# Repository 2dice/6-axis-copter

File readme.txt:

■6軸コプター概要
6軸に移動可能なマルチコプターを6個のプロペラで実現することを目標としている．
最終的には自動で衝突回避・PCからコマンドを受信しアクロバットな動きをさせる．

■開発フェーズ
ラフ設計段階
・電子回路
	1x基板(コアレス->ブラシモータ)浮力不足により2xでブラシレスモータ試作
	2x基板作成中
・アクチュエータ
	ブラシレスモータ・プロペラ仮選定済み．2xで浮力確認
・ソフトウェア
	デバイスドライバ仮実装完了．
	2x基板作成後最終確認．その後モータ制御実装．
・筐体
	2x向け設計完了(3Dプリント中)

■ディレクトリ構成
./datasheet
	電子回路に使用している部品のデータシート置き場
./devlog
	開発記録
./schematic
	**.sch
		回路図(kicad)
	**.kicad_pcb
		基板図(kicad)
	librarys
		回路図に使用したライブラリ(kicad)
	gbr
		P板.com提出ファイル(板厚0.6mmで発注)
	**.pdf
		回路図
	**.FCStd
		筐体3D-CAD設計ファイル(FreeCAD)
	**.stl
		DMM.make提出ファイル(3Dプリンタ用STLファイル)
./src
	ソフトウェア
	環境構築は以下を参照
	http://qiita.com/2dice/items/70c5abf6259508660bce
./src/tools/6-axis-monitor
	無線通信(zigbee)によるモニタツール(Qt)
	zigbee環境構築方法は作成中

■構成
・プロペラ配置は3d図面及び./devlog/pictureを参照
・ブラシレスモータとリポバッテリ(3セル直列)を使用
・移動量は3軸ジャイロ及び3軸加速度センサでモニタ
・EEPROMにチューニングパラメータを保存
・測距センサを全軸に付け，衝突を回避するようなロジックを入れる
・デバイスの電源電圧の都合上4.5V/3.6Vの2電源を生成．
  本来I/Fにレベルシフタを入れるべきだが抵抗で保護し実力で故障回避を狙う．
  そのため電源電圧を極力近づける設計とした．

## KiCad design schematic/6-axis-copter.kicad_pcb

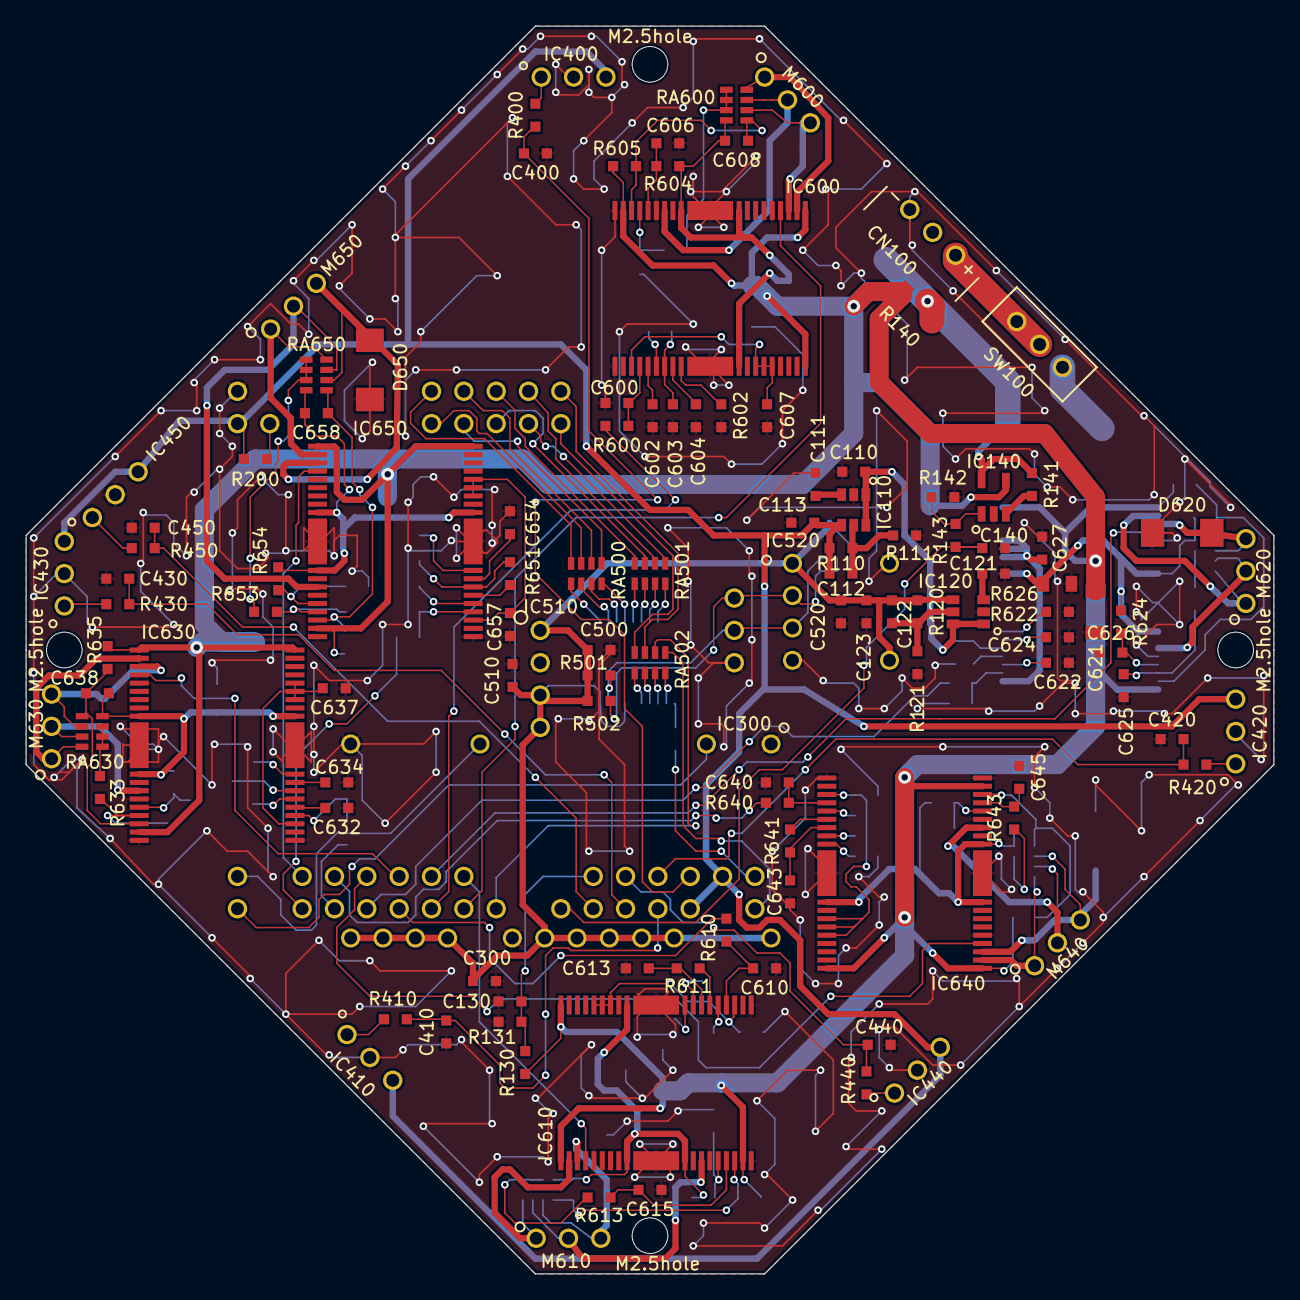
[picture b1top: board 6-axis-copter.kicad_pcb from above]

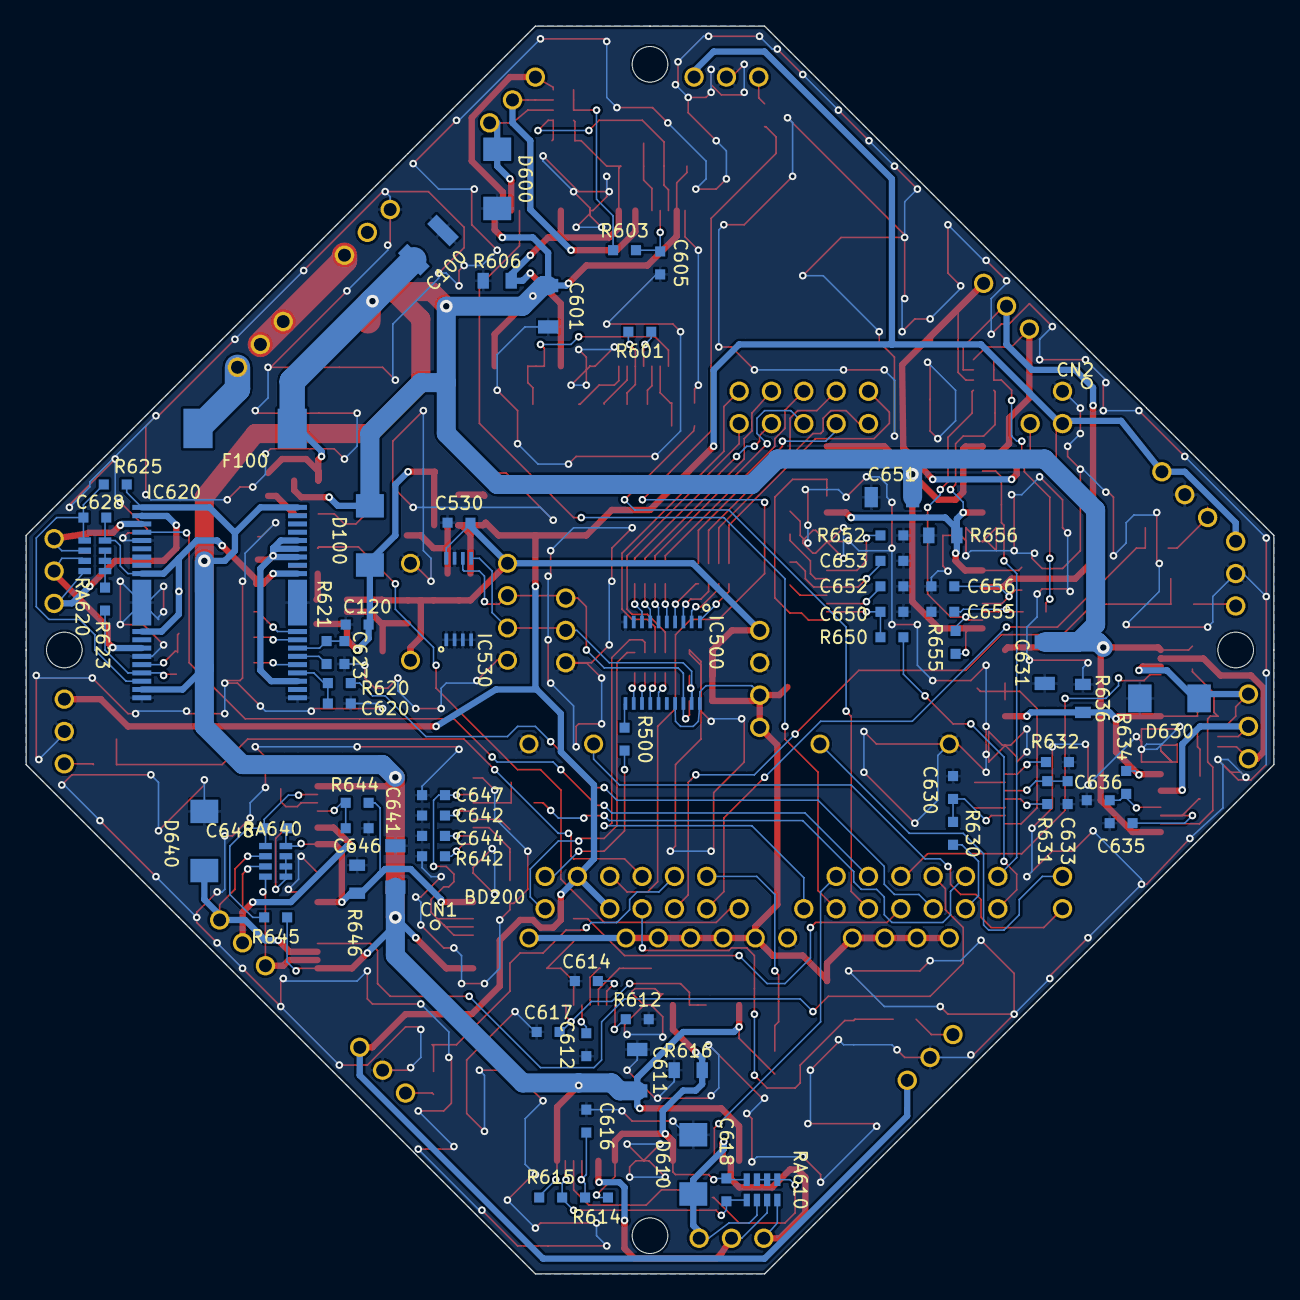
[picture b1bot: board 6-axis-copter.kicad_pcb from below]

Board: 2 copper layers, 98.0 x 98.0 mm, 188 parts (69 on the bottom side), 161 nets.

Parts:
BD200: H8-PRO
C100: 3225
C110, C111, C112, C113, C120, C121, C122, C123, C130, C140, C300, C400, C410, C420, C430, C440, C450, C500, C510, C520, C530, C600, C602, C603, C604, C605, C606, C607, C608, C610, C612, C613, C614, C615, C616, C617, C618, C620, C622, C623, C624, C625, C626, C627, C628, C630, C632, C633, C634, C635, C636, C637, C638, C640, C642, C643, C644, C645, C646, C647, C648, C650, C652, C653, C654, C655, C656, C657, C658: 1608
C601, C611, C621, C631, C641, C651: 3216
CN100: S3B-XH-A
D100, D600, D610, D620, D630, D640, D650: SR54F
F100: MF-SM300
IC110, IC120: SOT23-6
IC140: TSOP23-5
IC300: TWE-LITE
IC400, IC410, IC420, IC430, IC440, IC450: GP2Y0A21YK
IC500: TSSOP20
IC510: ADXL345
IC520: AE-L3GD20
IC530: TSSOP8
IC600, IC610, IC620, IC630, IC640, IC650: TB6588FG
M2.5hole, M2.5hole#2, M2.5hole#3, M2.5hole#4: M2.5hole
M600, M610, M620, M630, M640, M650: HK-AP05
R110, R111, R120, R121, R130, R131, R141, R142, R143, R200, R400, R410, R420, R430, R440, R450, R500, R501, R502, R600, R601, R602, R603, R604, R605, R610, R611, R612, R613, R614, R615, R620, R621, R622, R623, R624, R625, R630, R631, R632, R633, R634, R635, R640, R641, R642, R643, R644, R645, R650, R651, R652, R653, R654, R655: 1608
R140: 3216
R606, R616, R626, R636, R646, R656: 2012
RA500, RA501, RA502, RA600, RA610, RA620, RA630, RA640, RA650: BCN164AB
SW100: SS12D01G4

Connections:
+BATT: C601.1, C611.1, C621.1, C631.1, C641.1, C651.1, D100.1, IC140.4, IC600.1, IC600.17, IC600.36, IC610.1, IC610.17, IC610.36, IC620.1, IC620.17, IC620.36, IC630.1, IC630.17, IC630.36, IC640.1, IC640.17, IC640.36, IC650.1, IC650.17, IC650.36, R130.1, R140.2, R605.2, R615.2, R625.2, R635.2, R645.2, R655.2
/A0: BD200.61, RA502.7
/A1: BD200.62, RA502.8
/BAT_I: BD200.19, C140.1, R143.2
/BAT_V: BD200.18, C130.1, R130.2, R131.2
/D8: BD200.53, RA500.8
/D9: BD200.54, RA500.7
/D10: BD200.55, RA500.6
/D11: BD200.56, RA500.5
/D12: BD200.57, RA501.8
/D13: BD200.58, RA501.7
/D14: BD200.59, RA501.6
/D15: BD200.60, RA501.5
/DISTANCE_1: BD200.12, C400.1, R400.2
/DISTANCE_2: BD200.13, C410.1, R410.2
/DISTANCE_3: BD200.14, C420.1, R420.2
/DISTANCE_4: BD200.15, C430.1, R430.2
/DISTANCE_5: BD200.16, C440.1, R440.2
/DISTANCE_6: BD200.17, C450.1, R450.2
/MOTOR_1_IR: C608.1, IC600.9, IC600.10, IC600.28, R604.2, R606.1, RA600.4
/MOTOR_1_WAVEM: C608.2, IC600.16, R605.1, RA600.5
/MOTOR_2_IR: C618.1, IC610.9, IC610.10, IC610.28, R614.2, R616.1, RA610.4
/MOTOR_2_WAVEM: C618.2, IC610.16, R615.1, RA610.5
/MOTOR_3_IR: C628.1, IC620.9, IC620.10, IC620.28, R624.2, R626.1, RA620.4
/MOTOR_3_WAVEM: C628.2, IC620.16, R625.1, RA620.5
/MOTOR_4_IR: C638.1, IC630.9, IC630.10, IC630.28, R634.2, R636.1, RA630.4
/MOTOR_4_WAVEM: C638.2, IC630.16, R635.1, RA630.5
/MOTOR_5_IR: C648.1, IC640.9, IC640.10, IC640.28, R644.2, R646.1, RA640.4
/MOTOR_5_WAVEM: C648.2, IC640.16, R645.1, RA640.5
/MOTOR_6_IR: C658.1, IC650.9, IC650.10, IC650.28, R654.2, R656.1, RA650.4
/MOTOR_6_WAVEM: C658.2, IC650.16, R655.1, RA650.5
/MOTOR_DIR_1: BD200.25, IC600.4
/MOTOR_DIR_2: BD200.26, IC610.4
/MOTOR_DIR_3: BD200.28, IC620.4
/MOTOR_DIR_4: BD200.30, IC630.4
/MOTOR_DIR_5: BD200.32, IC640.4
/MOTOR_DIR_6: BD200.36, IC650.4
/MOTOR_PWM_1: BD200.27, R600.1
/MOTOR_PWM_2: BD200.29, R610.1
/MOTOR_PWM_3: BD200.31, R620.1
/MOTOR_PWM_4: BD200.33, R630.1
/MOTOR_PWM_5: BD200.34, R640.1
/MOTOR_PWM_6: BD200.35, R650.1
/ZIGBEE_Rx: BD200.39, IC300.3
/ZIGBEE_Tx: BD200.40, IC300.10
/~CS1: BD200.23, RA502.6
/~HWR: BD200.8, R500.2
/~RD: BD200.7, RA502.5
GND: BD200.41, C100.2, C110.2, C111.2, C113.2, C120.2, C121.2, C123.2, C130.2, C140.2, C300.2, C400.2, C410.2, C420.2, C430.2, C440.2, C450.2, C500.2, C510.2, C520.2, C530.2, C600.2, C601.2, C602.2, C603.2, C604.2, C605.2, C606.2, C607.2, C610.2, C611.2, C612.2, C613.2, C614.2, C615.2, C616.2, C617.2, C620.2, C621.2, C622.2, C623.2, C624.2, C625.2, C626.2, C627.2, C630.2, C631.2, C632.2, C633.2, C634.2, C635.2, C636.2, C637.2, C640.2, C641.2, C642.2, C643.2, C644.2, C645.2, C646.2, C647.2, C650.2, C651.2, C652.2, C653.2, C654.2, C655.2, C656.2, C657.2, CN100.1, D600.1, D610.1, D620.1, D630.1, D640.1, D650.1, IC110.2, IC120.2, IC140.2, IC300.1, IC300.14, IC300.20, IC400.2, IC410.2, IC420.2, IC430.2, IC440.2, IC450.2, IC500.10, IC510.2, IC510.7, IC520.4, IC520.8, IC530.1, IC530.2, IC530.3, IC530.4, IC530.7, IC600.5, IC600.13, IC600.18, IC600.19, IC600.37, IC600.38, IC610.5, IC610.13, IC610.18, IC610.19, IC610.37, IC610.38, IC620.5, IC620.13, IC620.18, IC620.19, IC620.37, IC620.38, IC630.5, IC630.13, IC630.18, IC630.19, IC630.37, IC630.38, IC640.5, IC640.13, IC640.18, IC640.19, IC640.37, IC640.38, IC650.5, IC650.13, IC650.18, IC650.19, IC650.37, IC650.38, R111.1, R121.1, R131.1, R142.1, R602.1, R606.2, R612.1, R616.2, R622.1, R626.2, R632.1, R636.2, R642.1, R646.2, R652.1, R656.2
unnamed: IC140.3, R141.1
unnamed: D630.2, IC630.3, M630.3, RA630.6
unnamed: C622.1, IC620.23
unnamed: C624.1, IC620.26
unnamed: C636.1, IC630.14, R634.1
unnamed: IC610.2, M610.1, RA610.8
unnamed: C617.1, IC610.21, IC610.30, IC610.31, IC610.32
unnamed: C604.1, IC600.26
unnamed: C612.1, IC610.23
unnamed: IC620.2, M620.1, RA620.8
unnamed: C627.1, IC620.21, IC620.30, IC620.31, IC620.32
unnamed: C614.1, IC610.26
unnamed: IC610.27, R612.2
unnamed: C637.1, IC630.21, IC630.30, IC630.31, IC630.32
unnamed: C635.1, IC630.15, R633.1
unnamed: IC630.27, R632.2
unnamed: IC630.24, R631.2
unnamed: C630.1, IC630.22, R630.2
unnamed: C633.1, IC630.25, R631.1
unnamed: C634.1, IC630.26
unnamed: C632.1, IC630.23
unnamed: C620.1, IC620.22, R620.2
unnamed: C623.1, IC620.25, R621.1
unnamed: IC620.24, R621.2
unnamed: C626.1, IC620.14, R624.1
unnamed: C625.1, IC620.15, R623.1
unnamed: IC620.27, R622.2
unnamed: D610.2, IC610.3, M610.3, RA610.6
unnamed: D620.2, IC620.3, M620.3, RA620.6
unnamed: R623.2, RA620.1, RA620.2, RA620.3
unnamed: C607.1, IC600.21, IC600.30, IC600.31, IC600.32
unnamed: C602.1, IC600.23
unnamed: IC600.2, M600.1, RA600.8
unnamed: IC620.12, M620.2, RA620.7
unnamed: IC650.27, R652.2
unnamed: C650.1, IC650.22, R650.2
unnamed: C653.1, IC650.25, R651.1
unnamed: IC650.24, R651.2
unnamed: C654.1, IC650.26
unnamed: C655.1, IC650.15, R653.1
unnamed: C652.1, IC650.23
unnamed: C644.1, IC640.26
unnamed: C647.1, IC640.21, IC640.30, IC640.31, IC640.32
unnamed: C642.1, IC640.23
unnamed: C656.1, IC650.14, R654.1
unnamed: IC650.2, M650.1, RA650.8
unnamed: R653.2, RA650.1, RA650.2, RA650.3
unnamed: C657.1, IC650.21, IC650.30, IC650.31, IC650.32
unnamed: D650.2, IC650.3, M650.3, RA650.6
unnamed: IC650.12, M650.2, RA650.7
unnamed: C646.1, IC640.14, R644.1
unnamed: IC640.27, R642.2
unnamed: C640.1, IC640.22, R640.2
unnamed: IC640.24, R641.2
unnamed: C643.1, IC640.25, R641.1
unnamed: R633.2, RA630.1, RA630.2, RA630.3
unnamed: IC630.12, M630.2, RA630.7
unnamed: IC630.2, M630.1, RA630.8
unnamed: D640.2, IC640.3, M640.3, RA640.6
unnamed: R643.2, RA640.1, RA640.2, RA640.3
unnamed: C645.1, IC640.15, R643.1
unnamed: IC640.12, M640.2, RA640.7
unnamed: IC640.2, M640.1, RA640.8
unnamed: IC500.12, RA502.4
unnamed: IC500.15, RA502.1
unnamed: BD200.44, R200.1
unnamed: C121.1, IC120.3
unnamed: CN100.3, SW100.1, SW100.2
unnamed: IC400.1, R400.1
unnamed: C122.2, IC120.5, R120.1, R121.2
unnamed: IC430.1, R430.1
unnamed: IC440.1, R440.1
unnamed: IC410.1, R410.1
unnamed: IC420.1, R420.1
unnamed: IC140.1, R142.2, R143.1
unnamed: F100.1, SW100.3
unnamed: C111.1, IC110.3
unnamed: C112.2, IC110.5, R110.1, R111.2
unnamed: IC500.14, RA502.2
unnamed: C100.1, F100.2, IC140.5, R140.1, R141.2
unnamed: C110.1, C120.1, D100.2, IC110.1, IC110.6, IC120.1, IC120.6
unnamed: IC500.18, IC510.9, IC520.2, IC530.6, R502.1
unnamed: IC500.19, IC510.8, IC520.3, IC530.5, R501.1
unnamed: IC500.6, RA501.2
unnamed: IC500.1, RA500.1
unnamed: IC500.2, RA500.2
unnamed: IC500.3, RA500.3
unnamed: IC500.4, RA500.4
unnamed: IC500.5, RA501.1
unnamed: IC500.7, RA501.3
unnamed: IC500.8, RA501.4
unnamed: IC500.11, R500.1
unnamed: IC500.13, RA502.3
unnamed: IC450.1, R450.1
unnamed: R603.2, RA600.1, RA600.2, RA600.3
unnamed: R613.2, RA610.1, RA610.2, RA610.3
unnamed: C606.1, IC600.14, R604.1
unnamed: D600.2, IC600.3, M600.3, RA600.6
unnamed: C605.1, IC600.15, R603.1
unnamed: IC600.12, M600.2, RA600.7
unnamed: C616.1, IC610.14, R614.1
unnamed: C613.1, IC610.25, R611.1
unnamed: IC610.12, M610.2, RA610.7
unnamed: C615.1, IC610.15, R613.1
unnamed: C610.1, IC610.22, R610.2
unnamed: IC610.24, R611.2
unnamed: C603.1, IC600.25, R601.1
unnamed: IC600.24, R601.2
unnamed: IC600.27, R602.2
unnamed: C600.1, IC600.22, R600.2
VCC: BD200.10, BD200.11, BD200.42, C112.1, C113.1, IC110.4, IC400.3, IC410.3, IC420.3, IC430.3, IC440.3, IC450.3, R110.2, R200.2
VDD: C122.1, C123.1, C300.1, C500.1, C510.1, C520.1, C530.1, IC120.4, IC300.15, IC300.16, IC300.17, IC300.18, IC300.21, IC300.22, IC300.23, IC300.24, IC300.25, IC300.28, IC500.17, IC500.20, IC510.1, IC510.3, IC510.4, IC520.1, IC520.5, IC530.8, R120.2, R501.2, R502.2

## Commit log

2014-08-23 書き込みテスト serialでhello worldを返すプログラム．水晶発振子25MHzでの書き込みテスト
2014-08-24 前プロジェクトを元にリファクタリング,VA=PA転送実装
2014-08-24 DRAM実装
2014-08-24 timer/timer割り込み実装
2014-08-24 周辺情報更新
2014-08-30 TIOCA0にPWM出力を実装
2014-08-30 TIOCA1にPWM出力を実装
2014-08-30 TIOCA2にPWM出力を実装
2014-08-30 TMO0にPWM出力を実装
2014-08-30 TMIO1にPWM出力を実装
2014-08-30 TMO2にPWM出力を実装
2014-08-31 makeでTAGSファイルを生成するようMakefileを修正
2014-08-31 IRQ5にプルアップ抵抗追加(オープンドレイン)
2014-09-06 回路図の不要な配線を削除
2014-09-07 AN0のAD値取得を実装
2014-09-08 AN1のAD値取得を実装
2014-09-08 リファクタリング(ADチャネルセレクトを汎用関数に切り出し)
2014-09-08 AN2~7のAD値取得を実装
2014-09-08 timer_init()からモータドライバの初期化を切り出してenable出力を追加
2014-09-15 I2Cバスコントローラ/加速度センサのデバイス情報追加
2014-09-15 TAGSファイルを生成する際に削除してから生成するように変更
2014-09-17 SCI2にzigbeeシリアル送信実装
2014-09-18 zigbeeからのコマンド受信割り込み実装
2014-09-20 SCI0をSCI1という記述に修正 SCI1に対し勘違いしてSCI0という名前をつけていたため
2014-10-04 I2Cバスコン及び加速度センサからのデータ読み出しを実装
2014-10-05 角速度センサからのデータ読み出しを実装
2014-10-05 リファクタリング(I2Cからの連続2バイト読みだし関数の変数名を汎用化)
2014-10-05 周辺情報の進捗更新
2014-10-05 角速度センサの読み出しを2バイト読み出しに変更
2014-10-05 モニタツール first commit(コンソールにD1の値のみを表示)
2014-10-05 モニタツールにD1を出力する簡易グラフ実装
2014-10-06 モニタツールで16進加速度データを物理値にして出力できるよう変更
2014-10-06 リファクタリング(データ格納関数を分離)
2014-10-06 モニタツールに全ての受信データ取り込みを実装
2014-10-08 モニタツールのAXにゼロ点補正と速度・距離計算を仮実装
2014-10-09 モニタツールの速度計算をブールの公式で再実装
2014-10-09 モニタツールに角度算出を実装(ブールの公式)
2014-10-11 回路図の配線ミスを修正
2014-10-11 回路図のバッテリーシンボル・フットプリント修正
2014-10-11 回路図のH8ボードフットプリントを修正
2014-10-11 回路図のモーターに直列にコイル追加
2014-10-11 回路図：DIP部品のサイズ修正
2014-10-11 回路図にバッテリーSW追加
2014-10-14 PCBボード図作成
2014-10-15 基板製造メーカー(P板.com)の指摘を元にPCBボード図を修正
2014-10-18 部品表作成
2014-10-18 readmeの進捗，ディレクトリ構成を更新
2014-10-26 周辺情報更新(筐体設計変更)
2014-10-31 周辺情報更新(筐体設計再変更)
2014-11-05 筐体仮作成
2014-11-08 筐体ASSY用スタンド作成
2014-11-13 モニタツールをQtで実装開始 シリアル入力をデバッグコンソールに出力
2014-11-14 モニタツール：シリアルのpublic変数・関数を極力privateに隠蔽
2014-11-15 dataクラス実装 serial_ifで受け取ったデータをdataクラスへ渡し格納
2014-11-16 モニタツール：シリアルデータの取りこぼしをなくすよう修正
2014-11-28 モニタツール：QMLでZ軸の加速度をグラフ表示 scene graphのサンプルコード"graph"をベースに作成
2014-11-29 浮力不足によりブラシレスモータに方針転換
2014-12-13 ブラシレスモータドライバデータシートまとめ
2015-01-10 モータ回転成功，浮力不足のためドライバ再選定が必要
2015-02-01 DRV11873で再挑戦．モータ回転せず，ドライバ再々選定が必要
2015-02-28 TB6588で再挑戦．ある程度浮力が出たため2x基板を作成(基板CADをkicadに変更)
2015-03-02 3Dプリンタ用筐体仮設計
2015-03-22 3Dプリンタ用筐体データ作成
2015-03-28 2x基板部品実装完了
2015-03-28 モニタツール：シリアルデータの取りこぼしを軽減
2015-03-29 10msで取得したセンサ値を80msで平均してシリアル出力する処理を実装
2015-04-04 モータdutyのgetter,setter実装
2015-04-04 UVLO実装
2015-04-29 バッテリ2S->3Sに変更しホバー仮実装．筐体破損のため再設計
2015-05-01 モニタツール：グラフを増殖しパネル状に配置
2015-06-13 筐体衝突時のモータ停止(OverShockLockOut)実装
2015-06-13 4.5V低下・モーター脱調を軽減するためハード改造 負荷が大きすぎたため5Vレギュレータ変更． モータードライバのカレントリミットを積分&回転数変動時の応答速度を遅くしモーター脱調を軽減． 電圧低下を軽減するためリポバッテリの容量増加しモーター直列に抵抗追加． 軽量化のため基板のNC_DIP_pin抜き&筐体足切断し縫い糸で補強
2015-06-20 姿勢制御に使用するセンサ値を平均値から移動平均値に変更
2015-06-20 姿勢制御に角速度センサ値を追加し回転抑制する処理を追加
2015-06-20 加速度センサ初期値を実測値から決定
2015-06-20 モニタツール：データ受信がなければグラフの更新を停止するように変更
2015-06-21 モニタツール：コマンド送信ボタン実装
